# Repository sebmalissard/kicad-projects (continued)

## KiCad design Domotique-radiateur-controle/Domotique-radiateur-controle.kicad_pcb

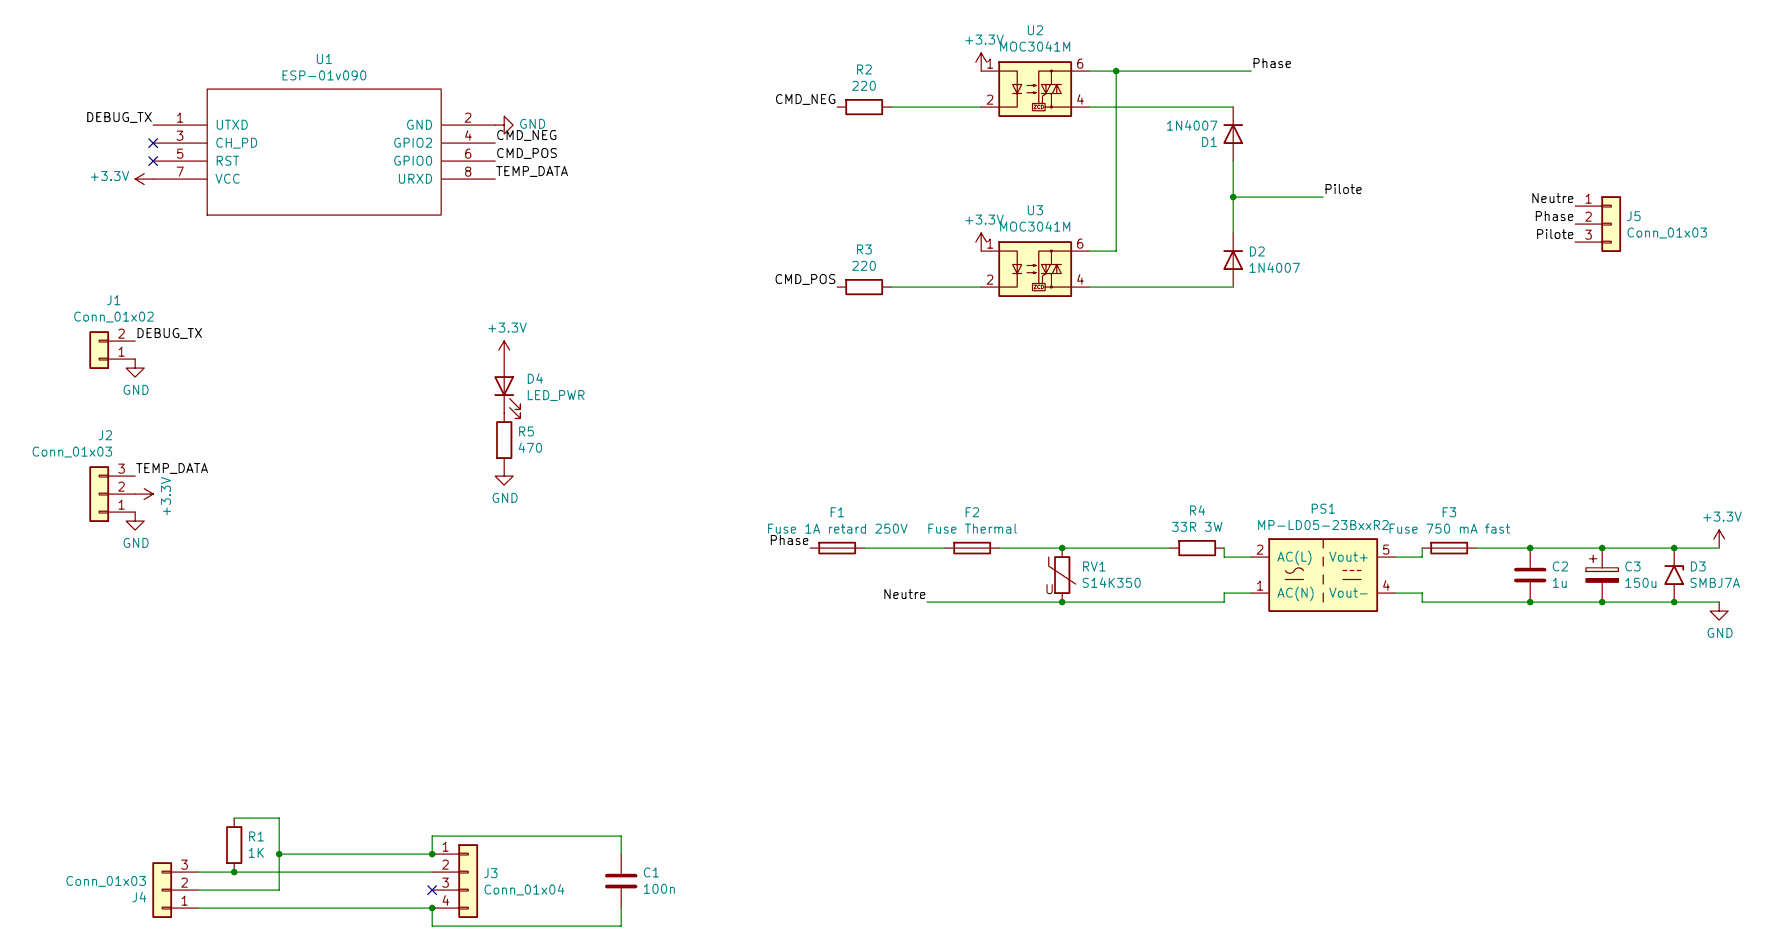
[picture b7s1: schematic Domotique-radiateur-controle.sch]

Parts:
C1: 100n; C_Disc_D5.0mm_W2.5mm_P5.00mm
C2: 1u; C_0805_2012Metric_Pad1.18x1.45mm_HandSolder
C3: 150u; CP_Radial_D5.0mm_P2.00mm
D1, D2: 1N4007; D_DO-41_SOD81_P10.16mm_Horizontal
D3: SMBJ7A; D_SMB
D4: LED_PWR; LED_D5.0mm
F1: Fuse 1A retard 250V; Fuseholder_Cylinder-5x20mm_Schurter_0031_8201_Horizontal_Op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
F2: Fuse Thermal; R_Axial_DIN0414_L11.9mm_D4.5mm_P20.32mm_Horizontal
F3: Fuse 750 mA fast; R_Axial_DIN0207_L6.3mm_D2.5mm_P10.16mm_Horizontal
J1: Conn_01x02; Molex_SL_171971-0002_1x02_P2.54mm_Vertical
J2, J4: Conn_01x03; Molex_SL_171971-0003_1x03_P2.54mm_Vertical
J3: Conn_01x04; PinHeader_1x04_P2.54mm_Vertical
J5: Conn_01x03; TerminalBlock_Phoenix_MKDS-1,5-3_1x03_P5.00mm_Horizontal
PS1: MP-LD05-23BxxR2; Converter_ACDC_Multicomp_MP-LD05-23BxxR2_THT
R1: 1K; R_Axial_DIN0207_L6.3mm_D2.5mm_P7.62mm_Horizontal
R2, R3: 220; R_0805_2012Metric_Pad1.20x1.40mm_HandSolder
R4: 33R 3W; R_Axial_DIN0617_L17.0mm_D6.0mm_P20.32mm_Horizontal
R5: 470; R_Axial_DIN0207_L6.3mm_D2.5mm_P7.62mm_Horizontal
RV1: S14K350; RV_Disc_D15.5mm_W4.5mm_P7.5mm
U1: ESP-01v090; PinHeader_2x04_P2.54mm_Vertical
U2, U3: MOC3041M; DIP-6_W7.62mm

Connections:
+3V3: C2.1, C3.1, D3.1 (A1), D4.2 (A), F3.1, J2.2, U1.7 (VCC), U2.1, U3.1
/CMD_NEG: R2.2, U1.4 (GPIO2)
/CMD_POS: R3.2, U1.6 (GPIO0)
/DEBUG_TX: J1.2, U1.1 (UTXD)
/Neutre: J5.1, PS1.1 (AC(N)), RV1.2
/Phase: F1.2, J5.2, U2.6, U3.6
/Pilote: D1.2 (A), D2.1 (K), J5.3
/TEMP_DATA: J2.3, U1.8 (URXD)
GND: C2.2, C3.2, D3.2 (A2), J1.1, J2.1, PS1.4 (Vout-), R5.2, U1.2 (GND)
unnamed: C1.1, J3.1, J4.2, R1.1
unnamed: C1.2, J3.4, J4.1
unnamed: D1.1 (K), U2.4
unnamed: D2.2 (A), U3.4
unnamed: D4.1 (K), R5.1
unnamed: F1.1, F2.2
unnamed: F2.1, R4.2, RV1.1
unnamed: F3.2, PS1.5 (Vout+)
unnamed: J3.2, J4.3, R1.2
unnamed: PS1.2 (AC(L)), R4.1
unnamed: R2.1, U2.2
unnamed: R3.1, U3.2

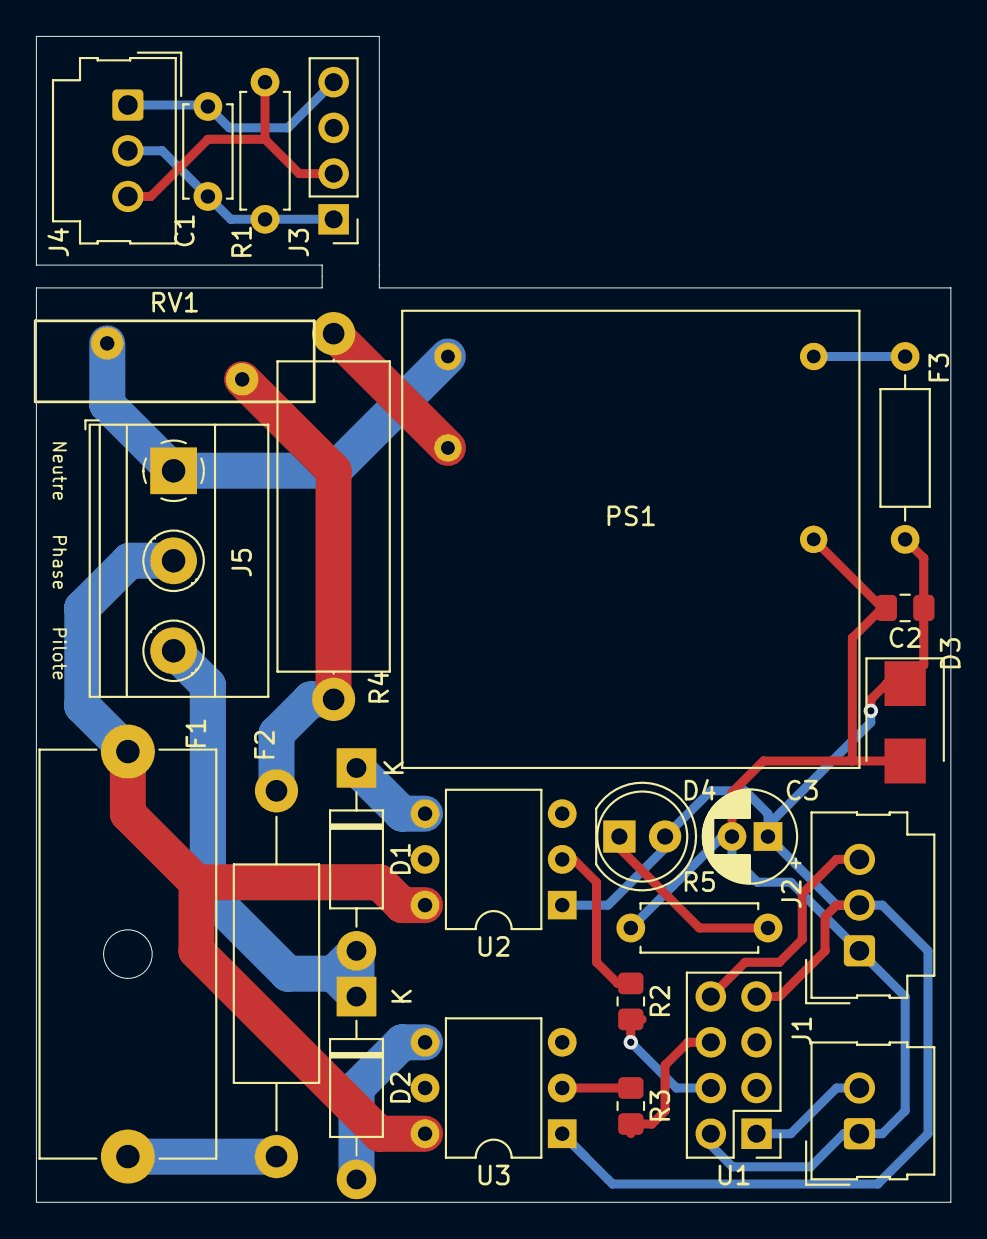
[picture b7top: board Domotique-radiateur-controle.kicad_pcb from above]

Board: 2 copper layers, 50.8 x 64.8 mm, 25 parts (0 on the bottom side), 21 nets.

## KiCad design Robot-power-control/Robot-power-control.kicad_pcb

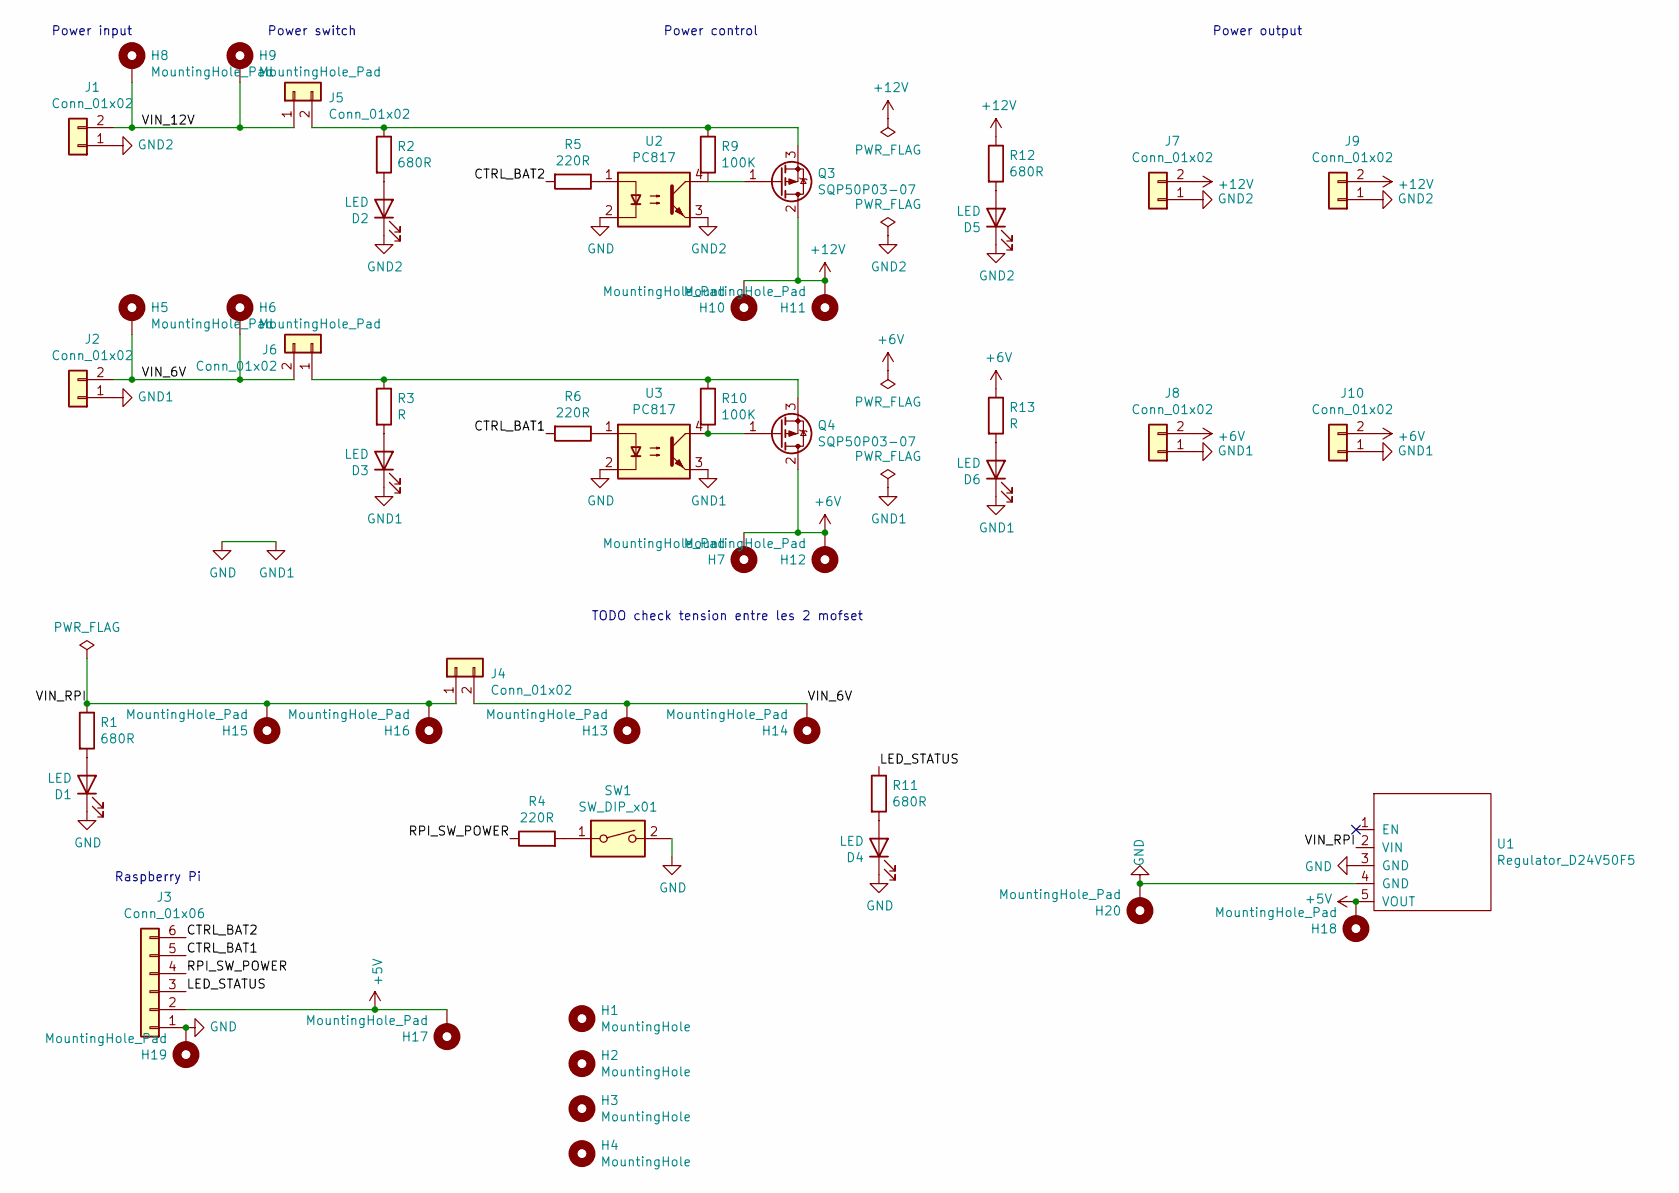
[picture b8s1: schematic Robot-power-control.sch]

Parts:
D1, D2, D3, D4, D5, D6: LED; LED_D5.0mm
H1, H2, H3, H4: MountingHole; MountingHole_3.2mm_M3
H5, H6, H7, H8, H9, H10, H11, H12: MountingHole_Pad; MountingHole_1.5mm_Pad
H13, H14, H15, H16, H17, H18, H19, H20: MountingHole_Pad; MountingHole_1.0mm_Pad
J1, J2, J4, J5, J6, J7, J8, J9, J10: Conn_01x02; Molex_Micro-Fit_3.0_43650-0215_1x02_P3.00mm_Vertical
J3: Conn_01x06; Molex_SL_171971-0006_1x06_P2.54mm_Vertical
Q3, Q4: SQP50P03-07; TO-220-3_Vertical
R1, R2, R11, R12: 680R; R_Axial_DIN0207_L6.3mm_D2.5mm_P7.62mm_Horizontal
R3, R13: R; R_Axial_DIN0207_L6.3mm_D2.5mm_P7.62mm_Horizontal
R4, R5, R6: 220R; R_Axial_DIN0207_L6.3mm_D2.5mm_P7.62mm_Horizontal
R9, R10: 100K; R_Axial_DIN0207_L6.3mm_D2.5mm_P7.62mm_Horizontal
SW1: SW_DIP_x01; SW_PUSH_6mm_H9.5mm
U1: Regulator_D24V50F5; Pololu_reg15d
U2, U3: PC817; DIP-4_W7.62mm

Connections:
+5V: H17.1, H18.1, J3.2, U1.5 (VOUT)
+6V: H7.1, H12.1, J8.2, J10.2, Q4.2 (D), R13.1
+12V: H10.1, H11.1, J7.2, J9.2, Q3.2 (D), R12.1
/CTRL_BAT1: J3.5, R6.2
/CTRL_BAT2: J3.6, R5.2
/LED_STATUS: J3.3, R11.1
/RPI_SW_POWER: J3.4, R4.1
/VIN_6V: H5.1, H6.1, H13.1, H14.1, J2.2, J4.2, J6.2
/VIN_12V: H8.1, H9.1, J1.2, J5.1
/VIN_RPI: H15.1, H16.1, J4.1, R1.1, U1.2 (VIN)
GND: D1.1 (K), D3.1 (K), D4.1 (K), D6.1 (K), H19.1, H20.1, J2.1, J3.1, J8.1, J10.1, SW1.2, U1.3 (GND), U1.4 (GND), U2.2, U3.2, U3.3
GND2: D2.1 (K), D5.1 (K), J1.1, J7.1, J9.1, U2.3
unnamed: D1.2 (A), R1.2
unnamed: D2.2 (A), R2.2
unnamed: D3.2 (A), R3.2
unnamed: D4.2 (A), R11.2
unnamed: D5.2 (A), R12.2
unnamed: D6.2 (A), R13.2
unnamed: J5.2, Q3.3 (S), R2.1, R9.1
unnamed: J6.1, Q4.3 (S), R3.1, R10.1
unnamed: Q3.1 (G), R9.2, U2.4
unnamed: Q4.1 (G), R10.2, U3.4
unnamed: R4.2, SW1.1
unnamed: R5.1, U2.1
unnamed: R6.1, U3.1

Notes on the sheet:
Power input
Power output
TODO check tension entre les 2 mofset
Power switch
Power control
Raspberry Pi

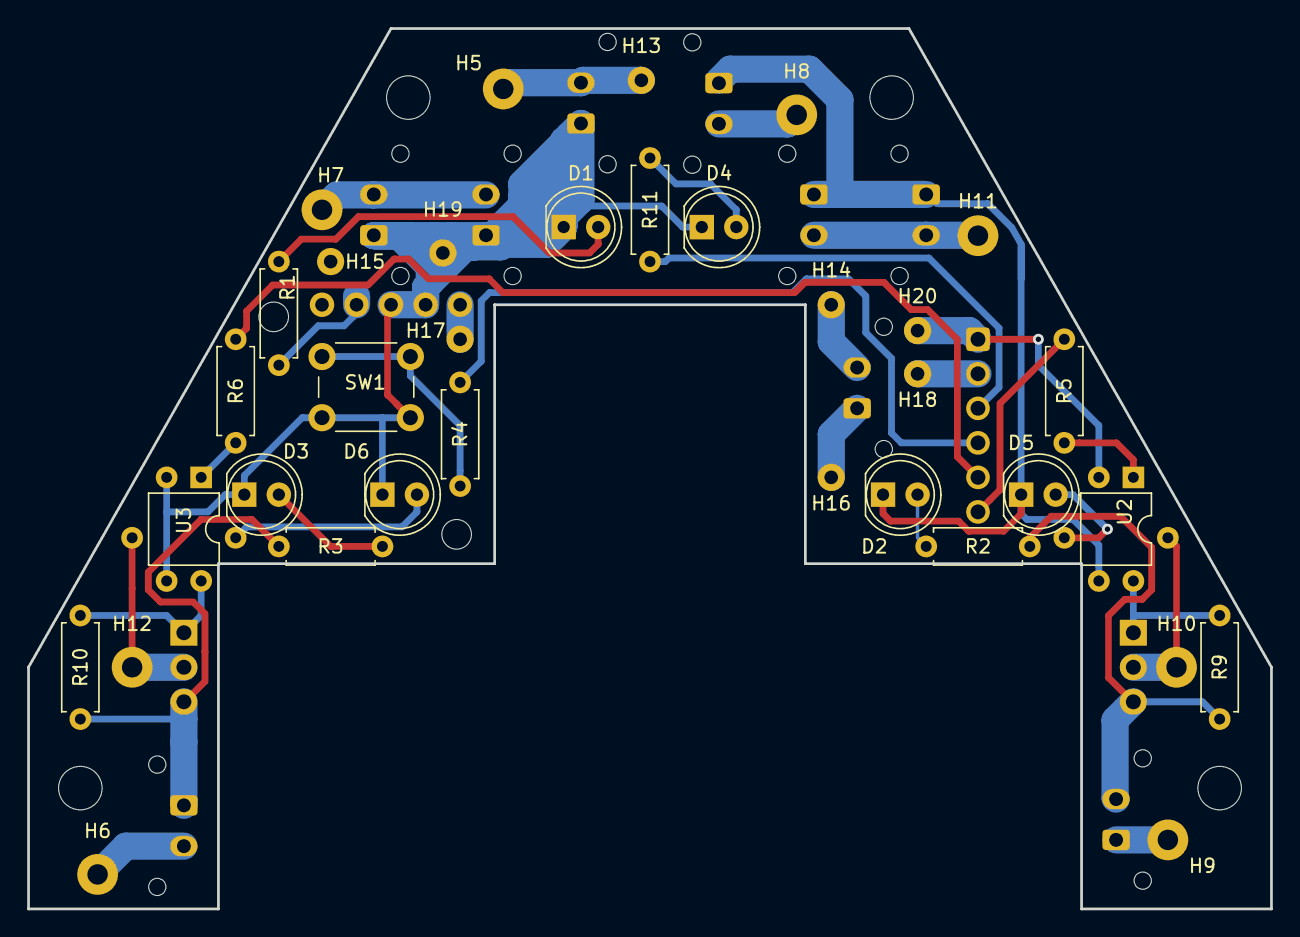
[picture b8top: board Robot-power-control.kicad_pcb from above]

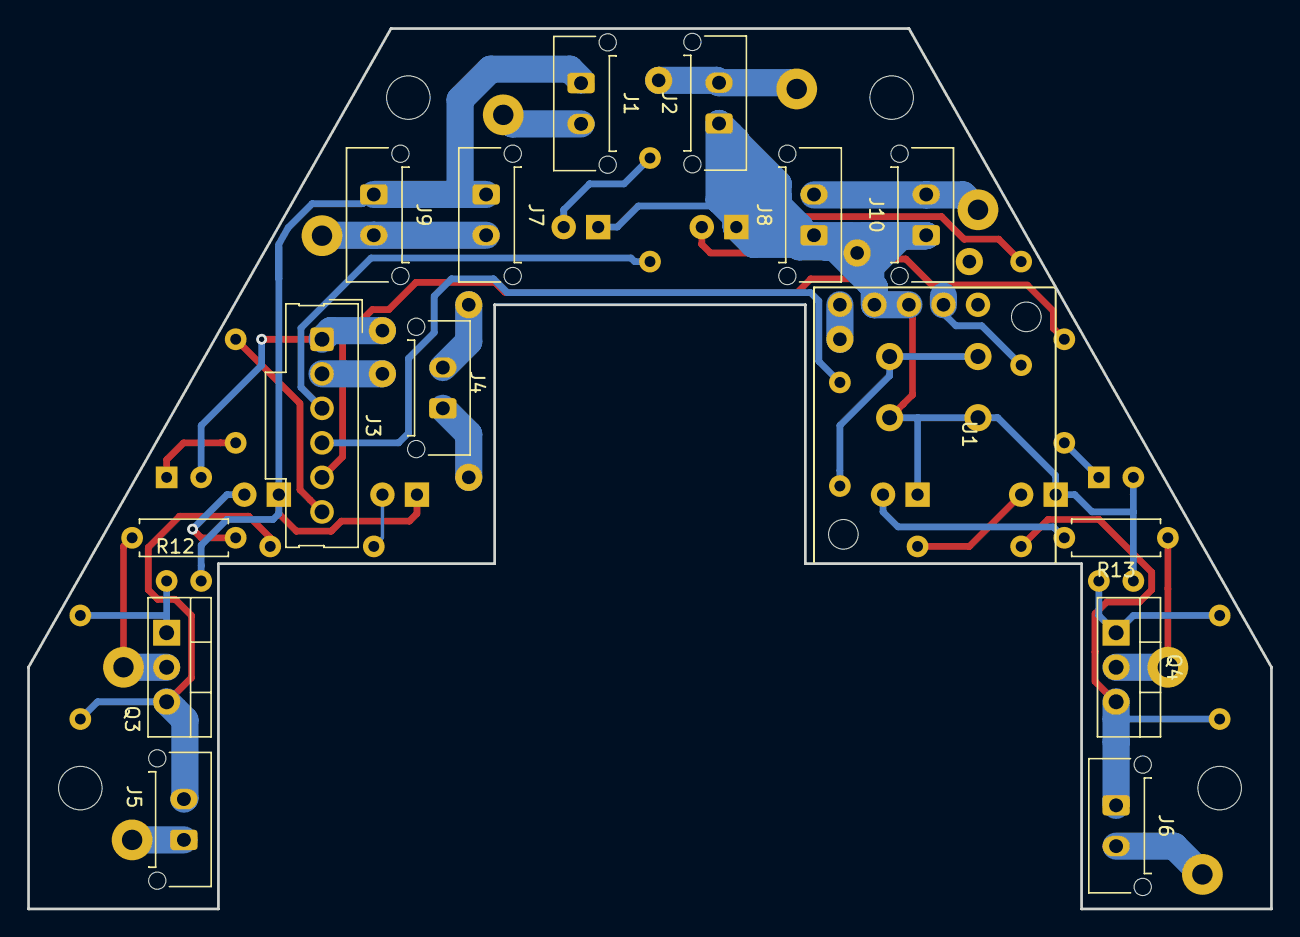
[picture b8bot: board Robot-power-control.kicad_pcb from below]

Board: 2 copper layers, 91.4 x 64.8 mm, 53 parts (15 on the bottom side), 25 nets.

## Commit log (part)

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2019-06-02 Add Robot-HMI
2019-10-28 Robot HMI v1
2019-11-29 Robot HMI - PCB
2020-11-07 Import Robot-propulsion-v2 projects
2020-11-07 Move Robot-HMI pcb files in a directory
2020-11-08 Robot HMI: Sync promicro and update resistences value
2020-11-09 Add Robot_propulsion_layer1_v3
2020-11-12 Add Robot-power-control
2020-12-06 Update Robot-power-control - PCB command
2021-12-14 Add Robot-propulsion-v2.2
2022-11-09 Add Domotique Radiateur Controle
2022-11-09 Add .gitignore
2023-01-07 Update Domotiqua radiateur controle - Add Neutre Phase Pilote indication on PCB
2023-11-17 Add Domotique temperature sonde draft
2023-11-17 Add Domotique keyboard et LED RGB WIP
2024-04-12 Domotique temperature sonde: Remove subdirectory
2024-10-27 Domotique-Keyboard-et-LED-RGB: Version 1
2026-06-21 Add Linky TIC schematic
